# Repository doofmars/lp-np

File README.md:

lp-np
=====

The Low Profile - Numpad (lp-np) is my first attempt at creating my own PCB from scratch.
This was done with the long-lasting wish to create some hardware.
A keyboard (numpad in this case) is a first project with less complexity on the used parts and hardware.
In the past I gathered some experience in ordering and soldering a [Corne](https://github.com/foostan/crkbd) keyboard
and for creating this project I used the KiCad files as a template.
This helped me to get the right schematic and after some trial and error a layout that looks right.

**2025-11-09**: Assembly done

**2025-10-28**: PCB has arrived

**2025-10-15**: PCB is done next order all required parts and 3d-printing.

## Parts and PCB footprint

The PCB design would not been possible without the aid of the [Corne](https://github.com/foostan/crkbd) keyboard project
where the base footprint for the used ProMicro and display header originate from.
For the switches I got my hands on the Cherry MX ULP (Ultra Low Profile) Switches which
are pretty well documented in [the repo of pashutk](https://github.com/pashutk/Cherry_MX_ULP/tree/main).
Here example projects, footprints, datasheets and sourcing information can be found.

## Caps

For the caps, I resorted to 3D printing my own.
A base model can be found in the [zmk-config-mikefive repo of mikeholscher](https://github.com/mikeholscher/zmk-config-mikefive/).
This repo uses _Kailh PG1316S_ switches, which have a similar footprint to Cherry switches.
Keycap.step files for 3D printing can be found in the repository.

# Bill of Materials (BOM)

| Reference | Component Description                               | Value      | Amount |
|:----------|:----------------------------------------------------|:-----------|:-------|
| U         | ProMicro (or compatible derivate)                   |            | 1      |
| U-Header  | Generic connector, single row,                      | Conn_01x12 | 2      |
| J         | Generic connector, single row, 01x04                | Conn_01x04 | 1      |
| RSW1      | Momentary Tact Tactile Push Button Switch 2 Pin DIP | 3x6        | 1      |
| OLED      | Mini 0.91 Inch 128x32 OLED                          | Optional   | 1      |
| D         | Diode (SOD-123)                                     | D          | 20     |
| SW        | Cherry MX ULP (Ultra Low Profile) Switches          | SW_Push    | 20     |

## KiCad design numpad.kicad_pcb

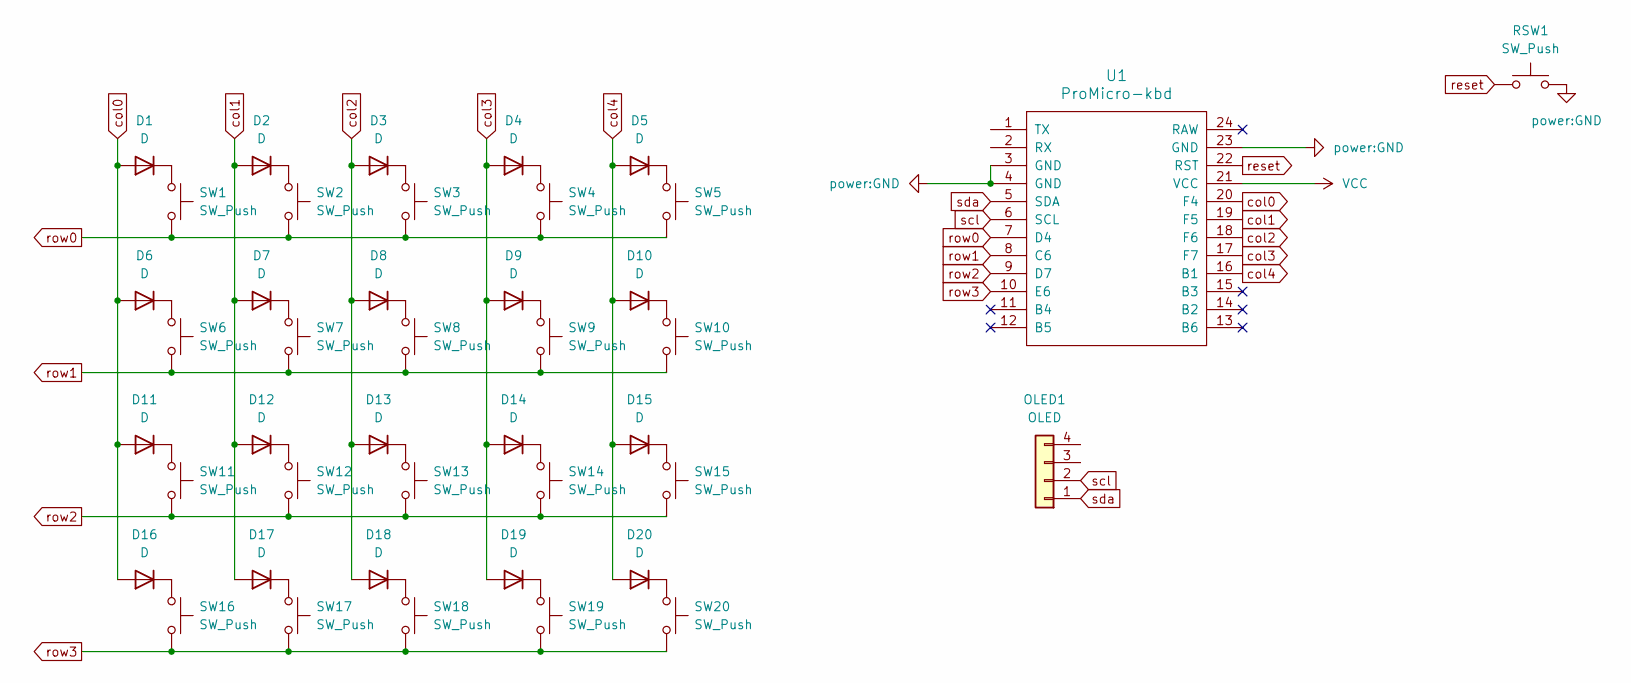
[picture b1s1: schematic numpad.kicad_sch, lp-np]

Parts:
D1, D2, D3, D4, D5, D6, D7, D8, D9, D10, D11, D12, D13, D14, D15, D16, D17, D18, D19, D20: D; D_SOD-123
OLED1: OLED; OLED_generic
RSW1: SW_Push; Reset
SW1, SW2, SW3, SW4, SW5, SW6, SW7, SW8, SW9, SW10, SW11, SW12, SW13, SW14, SW15, SW16, SW17, SW18, SW19, SW20: SW_Push; Cherry_ULP_SMD
U1: ProMicro-kbd; ProMikcro

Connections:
GND: RSW1.2, U1.3 (GND), U1.4 (GND), U1.23 (GND); also elsewhere on the board
LED: U1.1 (TX)
unnamed: D1.1 (K), SW1.1
unnamed: D2.1 (K), SW2.1
unnamed: D3.1 (K), SW3.1
unnamed: D4.1 (K), SW4.1
unnamed: D5.1 (K), SW5.1
unnamed: D6.1 (K), SW6.1
unnamed: D7.1 (K), SW7.1
unnamed: D8.1 (K), SW8.1
unnamed: D9.1 (K), SW9.1
unnamed: D10.1 (K), SW10.1
unnamed: D11.1 (K), SW11.1
unnamed: D12.1 (K), SW12.1
unnamed: D13.1 (K), SW13.1
unnamed: D14.1 (K), SW14.1
unnamed: D15.1 (K), SW15.1
unnamed: D16.1 (K), SW16.1
unnamed: D17.1 (K), SW17.1
unnamed: D18.1 (K), SW18.1
unnamed: D19.1 (K), SW19.1
unnamed: D20.1 (K), SW20.1
SCL: OLED1.2, U1.6 (SCL); also elsewhere on the board
SDA: OLED1.1, U1.5 (SDA); also elsewhere on the board
VCC: U1.21 (VCC); also elsewhere on the board
col0: D1.2 (A), D6.2 (A), D11.2 (A), D16.2 (A), U1.20 (F4)
col1: D2.2 (A), D7.2 (A), D12.2 (A), D17.2 (A), U1.19 (F5)
col2: D3.2 (A), D8.2 (A), D13.2 (A), D18.2 (A), U1.18 (F6)
col3: D4.2 (A), D9.2 (A), D14.2 (A), D19.2 (A), U1.17 (F7)
col4: D5.2 (A), D10.2 (A), D15.2 (A), D20.2 (A), U1.16 (B1)
col5: U1.15 (B3)
data: U1.2 (RX)
reset: RSW1.1, U1.22 (RST)
row0: SW1.2, SW2.2, SW3.2, SW4.2, SW5.2, U1.7 (D4)
row1: SW6.2, SW7.2, SW8.2, SW9.2, SW10.2, U1.8 (C6)
row2: SW11.2, SW12.2, SW13.2, SW14.2, SW15.2, U1.9 (D7)
row3: SW16.2, SW17.2, SW18.2, SW19.2, SW20.2, U1.10 (E6)

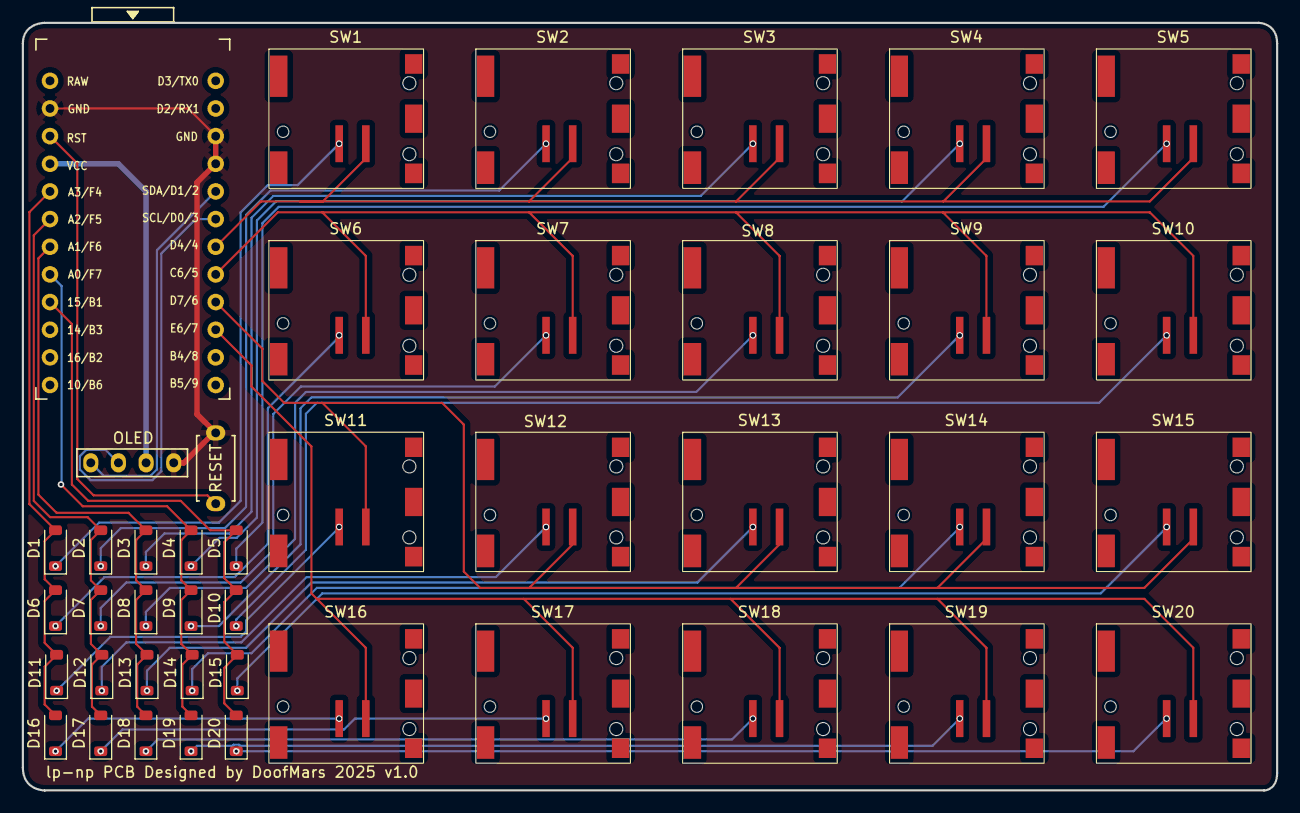
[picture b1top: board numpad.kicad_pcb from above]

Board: 2 copper layers, 115.2 x 70.5 mm, 43 parts (0 on the bottom side), 34 nets.

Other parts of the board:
OLED: OLED; OLED_1side

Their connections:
GND: OLED.4; also elsewhere on the board
SCL: OLED.2; also elsewhere on the board
SDA: OLED.1; also elsewhere on the board
VCC: OLED.3; also elsewhere on the board

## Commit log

2025-10-15 Fix typo
2025-10-28 Add gerber zip output to gitingore
2025-11-09 Update readme with latest progress
